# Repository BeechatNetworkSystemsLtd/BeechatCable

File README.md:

# Beechat Use-&-Charge cable
## _Flexible cable that allows charging your smartphone while using the Beechat Clip_

General
-------------------

The cable is a UFP (Upstream Facing Port) to DFP (Downstream Facing Port) device, for mobile device charging and data transmission, the DFP port is configured with a 10K resistor between the DC and Vbus pin of the USB-C male plug, which allows a current delivery of up to 3A for devices that require it, the UFP port is designed on a PCB (Printed circuit board), which has the functionality of connecting two FFC (Flexible flat cable) cables, for the transmission of power to the USB-C MALE, also in this design, we have two data transmission lines between the 2 FFC cables, to send and receive data between devices.

Repository content:
-------------------
- Hardware - all Eagle design files (.brd, .sch)
- Production- Gerber files.

Images:
-------------------

PCB USB-C FEMALE features
-------------------
* **Dimensions:** 14 * 14mm
* **DC resistors:** 5.1 k
* **4-position FFC cable connection pins. (x2)**
* **USB C male receptable connector** 5V (USB)

PCB USB C MALE features
-------------------
* **Dimensions:** 9.5 * 4mm
* **DC resistor:** 10k
* **4-position FFC cable connection pins. (x1)**
* **USB C Female plug Slim.**

Repository contents:
-------------------
**Project files_USBC_FEMALE:**
- 1_schematics.
- 2_PCB Layout.
- 3_BOM and CPL.
- 4_Gerber files.
- 5_Eagle files.
- 6_3D files.
- 7_Libraries.

**Project files_USBC_MALE:**
- 1_schematics.
- 2_PCB Layout.
- 3_BOM and CPL.
- 4_Gerber files.
- 5_Eagle files.
- 6_3D files.
- 7_Libraries.

Product versions:
-------------------
V1.0 

License Information
-------------------
The hardware is released under [Creative Commons ShareAlike 4.0 International](https://creativecommons.org/licenses/by-sa/4.0/).

Distributed as-is; no warranty is given.

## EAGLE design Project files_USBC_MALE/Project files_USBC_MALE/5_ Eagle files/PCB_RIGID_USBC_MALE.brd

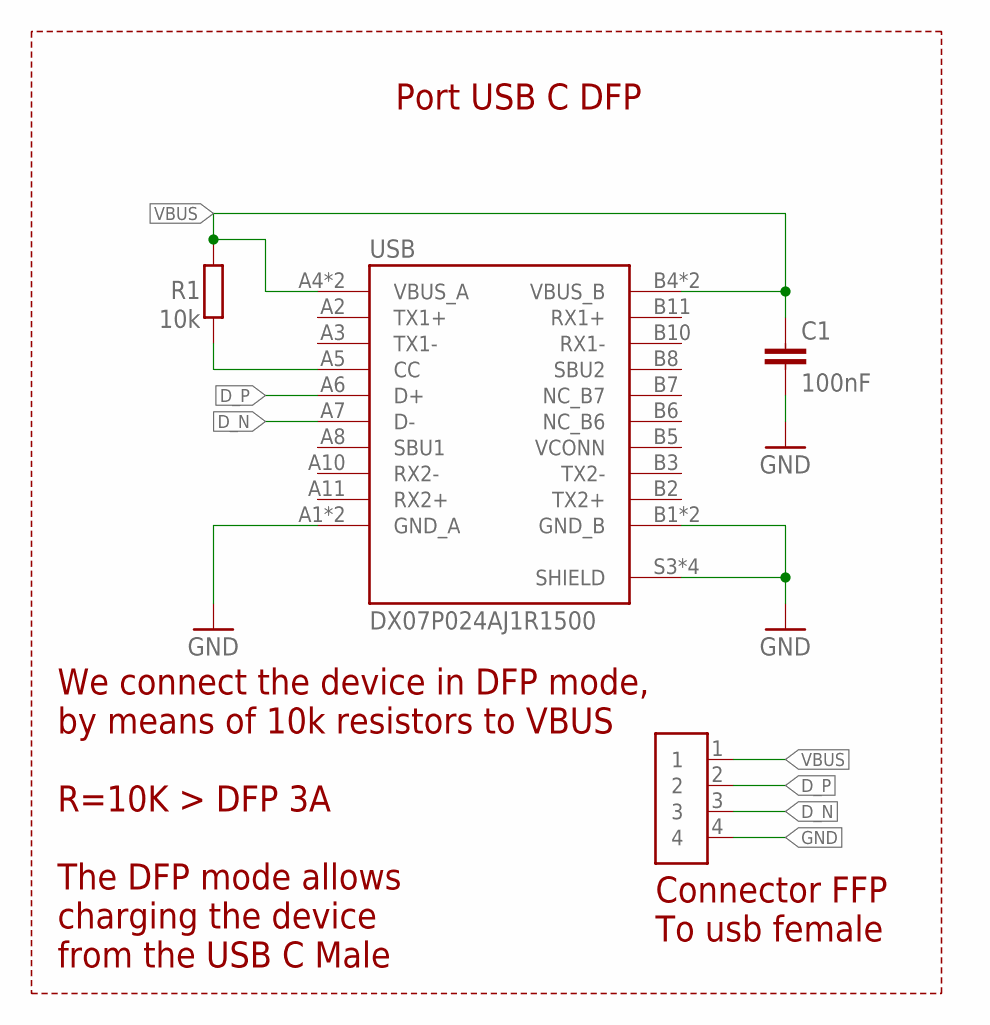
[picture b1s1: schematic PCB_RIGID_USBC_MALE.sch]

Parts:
C1: 100nF; C0603
FFP: CONN_FLEX_2.5MM
R1: 10k; R0603
USB: DX07P024AJ1R1500; JAE_DX07P024AJ1R1500

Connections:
D_N: FFP.3, USB.A7 (D-)
D_P: FFP.2, USB.A6 (D+)
GND: C1.2, FFP.4, USB.A1 (GND_A), USB.A12 (GND_A), USB.B1 (GND_B), USB.B12 (GND_B), USB.S3 (SHIELD), USB.S4 (SHIELD), USB.S5 (SHIELD), USB.S6 (SHIELD)
unnamed: R1.1, USB.A5 (CC)
VBUS: C1.1, FFP.1, R1.2, USB.A4 (VBUS_A), USB.A9 (VBUS_A), USB.B4 (VBUS_B), USB.B9 (VBUS_B)

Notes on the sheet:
Port USB C DFP
Connector FFP To usb female
We connect the device in DFP mode, by means of 10k resistors to VBUS R=10K > DFP 3A
The DFP mode allows charging the device from the USB C Male

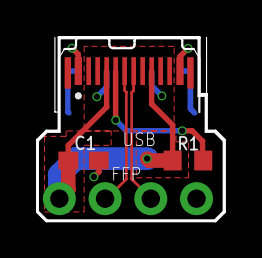
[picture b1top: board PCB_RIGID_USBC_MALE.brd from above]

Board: 2 copper layers, 10.4 x 10.2 mm, 4 parts (0 on the bottom side), 5 nets.

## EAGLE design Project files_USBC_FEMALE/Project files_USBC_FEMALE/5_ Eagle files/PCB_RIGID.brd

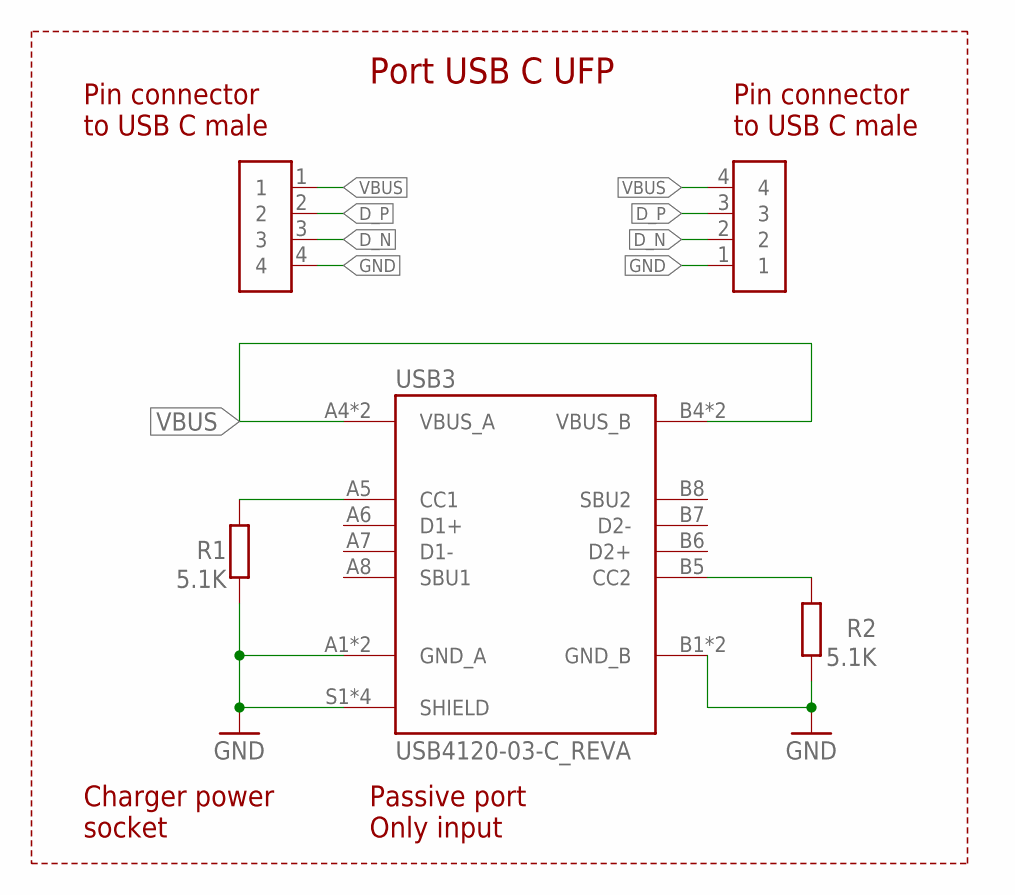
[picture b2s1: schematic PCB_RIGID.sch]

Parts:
R1, R2: 5.1K; R0603
USB1, USB2: CONN_FLEX_2.5MM
USB3: USB4120-03-C_REVA; GCT_USB4120-03-C_REVA

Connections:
D_N: USB1.3, USB2.2
D_P: USB1.2, USB2.3
GND: R1.1, R2.1, USB1.4, USB2.1, USB3.A1 (GND_A), USB3.A12 (GND_A), USB3.B1 (GND_B), USB3.B12 (GND_B), USB3.S1 (SHIELD), USB3.S2 (SHIELD), USB3.S3 (SHIELD), USB3.S4 (SHIELD)
unnamed: R1.2, USB3.A5 (CC1)
unnamed: R2.2, USB3.B5 (CC2)
VBUS: USB1.1, USB2.4, USB3.A4 (VBUS_A), USB3.A9 (VBUS_A), USB3.B4 (VBUS_B), USB3.B9 (VBUS_B)

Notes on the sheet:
Port USB C UFP
Passive port Only input
Charger power socket
Pin connector to USB C male

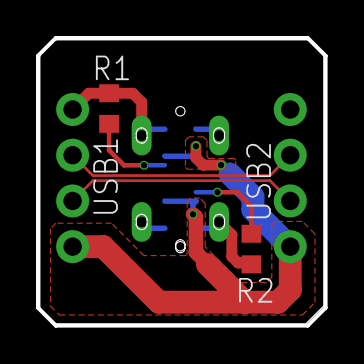
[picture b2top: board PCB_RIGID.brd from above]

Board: 2 copper layers, 16.0 x 16.0 mm, 5 parts (1 on the bottom side), 6 nets.

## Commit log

2021-11-27 First revision upload
